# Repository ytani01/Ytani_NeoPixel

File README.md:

# Ytani NeoPixel Library

## 1. for Python3 on Raspberry Pi
  [rpi-python3/](rpi-python3/)

## 2. for C++ on Arduino, ESP32, ATTiny etc..
  [arduino-etc/](arduino-etc/)

### 2.0 !! 重要 !!

* NeoPixelライブラリの実行で、割り込みが効かなくなる
  ``show()``の直後に、``interrupts()`` または ``sei()``をすること！
* ATTiny85のメモリ(RAM)不足で、挙動がおかしくなる。

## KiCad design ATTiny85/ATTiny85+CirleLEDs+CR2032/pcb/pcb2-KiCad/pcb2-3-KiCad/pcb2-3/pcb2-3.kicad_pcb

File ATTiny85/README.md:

# ATTiny85

## Arduio IEDによる書き込み

### ブートローダー

### ボード設定

- [ツール]-[ボード]-[ATTinyCore]-[ATTiny25/45/85 (No bootloader)]
- [ツール]-[Chip]-[ATTiny85]
- [ツール]-[書き込み装置]-[Arduino Leo/Micro as ISP (ATmega32U4)]

### ブートローダーの書き込み (最初の一回だけ)

- [ツール]-[ブートローダーを書き込む]

### 書き込み

- [スケッチ]-[書き込み装置を使って書き込む] (Ctrl+Shift+U)

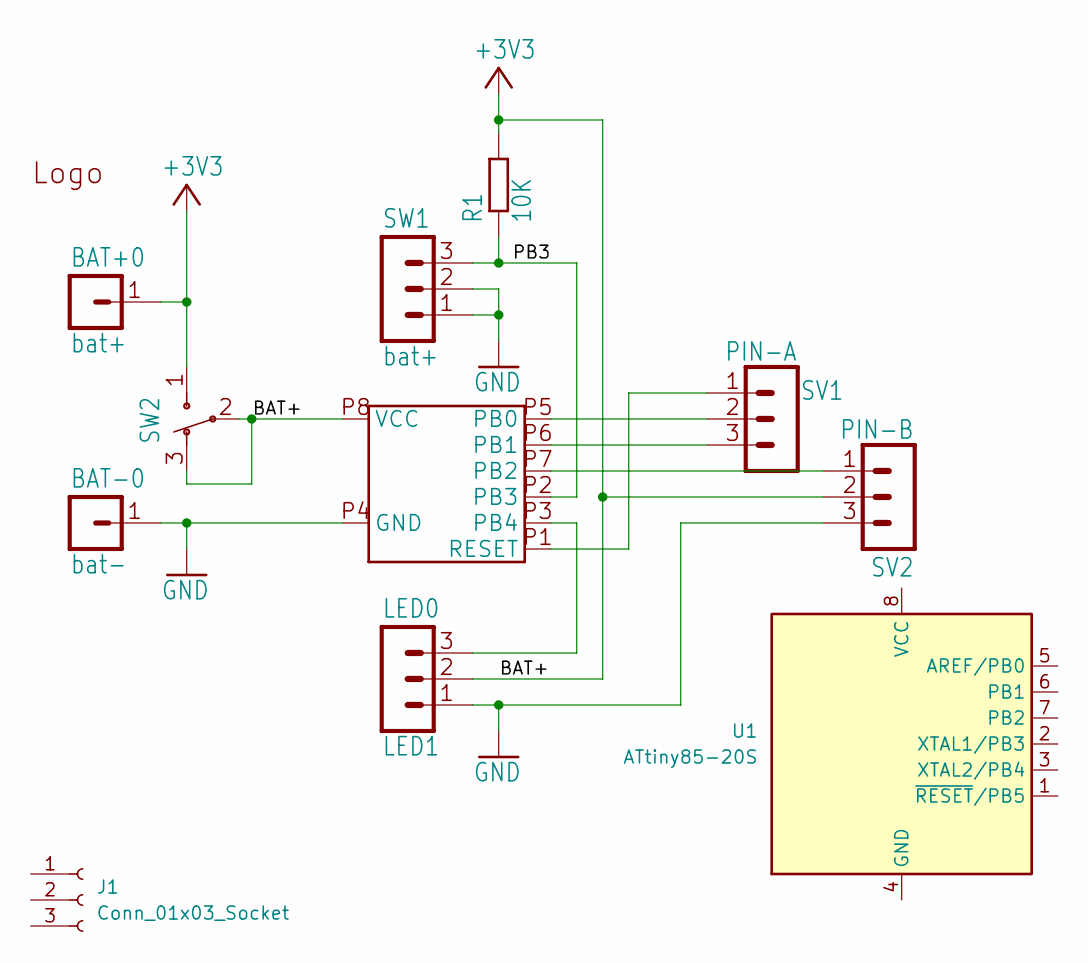
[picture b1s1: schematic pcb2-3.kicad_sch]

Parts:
ATTINY85-1: ATTINY85; ATTINY85-20SUR
BAT+0: bat+; PINHEAD-MA01-1
BAT-0: bat-; PINHEAD-MA01-1
J1: Conn_01x03_Socket
LED0: LED1; PINHEAD-MA03-1
LOGO1: LOGO-YT; LOGO-YT1
R1: 10K; M3216
SV1: PIN-A; PINHEAD-MA03-1
SV2: PIN-B; PINHEAD-MA03-1
SW1: bat+; PINHEAD-MA03-1
SW2: POWER; SW3-1
U1: ATtiny85-20S; SOIC-8_5.3x5.3mm_P1.27mm

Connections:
+3V3: ATTINY85-1.P8 (VCC), BAT+0.1, LED0.2, R1.2, SV2.2, SW2.1, SW2.2, SW2.3
/PB3: ATTINY85-1.P2 (PB3), R1.1, SW1.3
GND: ATTINY85-1.P4 (GND), BAT-0.1, LED0.1, SV2.3, SW1.1, SW1.2
unnamed: ATTINY85-1.P5 (PB0), SV1.2
unnamed: ATTINY85-1.P6 (PB1), SV1.3
unnamed: ATTINY85-1.P7 (PB2), SV2.1
unnamed: ATTINY85-1.P3 (PB4), LED0.3
unnamed: ATTINY85-1.P1 (RESET), SV1.1

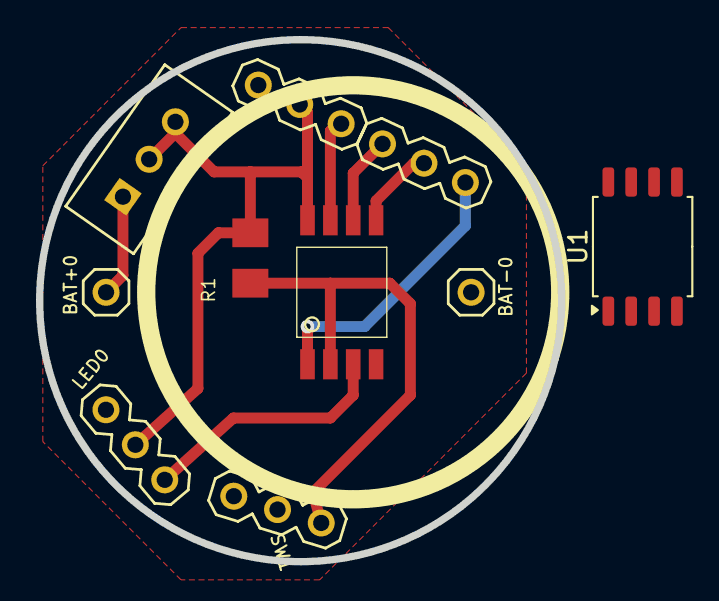
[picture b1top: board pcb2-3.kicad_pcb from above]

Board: 2 copper layers, 29.0 x 29.0 mm, 11 parts (1 on the bottom side), 8 nets.

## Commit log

2021-09-01 in preparation
2021-09-01 test1.py
2021-09-01 version 0.0.1
2021-09-01 UPD: README.md
2021-09-02 UPD: yt_neopixel.py
2021-09-02 UPD: rename
2021-09-02 UPD:
2021-09-02 ADD: test2
2021-09-02 UPD: __main__.py
2021-09-02 0.0.2
2021-09-02 START: 0.0.3
2021-09-02 ADD: Ytani_NeoPixel_Color class
2021-09-02 START: 0.0.4
2021-09-03 COMMIT: 0.0.4
2021-09-03 START: 0.0.5
2021-09-03 ADD: examples/robot_eye1.py
2021-09-05 UPD: tests
2021-09-05 START: 0.0.6
2021-09-05 ADD: class RobotEye_Cirle7LEDs
2021-09-05 START: 0.0.7
2021-09-06 UPD: class RobotEye_Cirle7LEDs
2021-09-06 UPD: robot_eyes_7leds.py
2021-09-06 FIX: install.sh
2021-09-06 START: 0.0.8
2021-09-06 ADD: RGB test
2021-09-06 START: 0.0.9
2021-09-06 UPD: for CuiLib 0.0.3
2021-09-06 START: 0.0.10
2021-09-06 START: 0.1.0
2021-09-07 UPD: README.md, setup.cfg
2021-09-10 START: 0.1.1
2021-09-12 UPD: add offset option to robot_eye1
2021-09-12 START: 0.1.2
2021-09-12 UPD: rgb-test
2021-09-12 START: 0.1.3
2021-09-13 UPD: robot_eye1
2021-09-13 START: 1.1.4
2021-09-13 START: 0.1.5
2021-09-15 UPD: update
2021-09-15 START: 1.1.6
2021-09-15 UPD: robot-eye
2021-09-16 UPD: dir tree
2021-09-16 ADD: arduino-c++
2021-09-18 ADD: color_wave2.ino
2021-09-18 UPD: color_wave2.ino
2021-09-20 UPD: demo
2021-09-20 UPD: robot_eye
2021-09-20 START: 0.1.7
2021-09-23 UPD: robot_eye_7leds.py
2021-09-25 ADD: Circle7LEDs-1.jpg
2021-09-28 START: 0.1.8
2021-09-28 ADD: interactive mode for robot-eye
2021-10-02 ADD: color_wave_4led/
2021-10-03 UPD: color_wave/
2021-10-05 ADD: tests/touch1
2021-10-06 UPD: tests/color_wave_ATTiny
2021-10-08 ADD: tests/switch1
2021-10-09 ADD: pcb
2021-10-09 ADD: pcb/bootloader
2021-10-09 UPD: .gitignore
2021-10-12 ADD: tests/color_wave3
2021-10-12 UPD: color_wave3
2021-11-18 UPD: pcb
2021-11-18 ADD: M5StampPico/
2021-11-18 ADD: M5StampPico/analogRead1/
2021-11-19 ADD: M5StampPico/sensor-NeoPixel/
2021-12-05 ADD: badge1/
2021-12-06 ADD: switch2/
2021-12-06 ADD: ATTiny-pinout.jpg
2021-12-07 ADD: switch3
2021-12-07 ADD: Mode_SingleColor
2021-12-07 UPD: switch3/
2021-12-10 ADD: pcb2/
2021-12-11 ADD: pcb3/
2021-12-12 ADD: LedLight2/
2021-12-12 UPD: LedLight2/
2021-12-13 ADD: LedLight3/Mode_White
2021-12-14 UPD: LedLight3/
2021-12-18 UPD: init.el
2021-12-20 ADD: ATTiny85/.../pcb2-2/
2021-12-22 ADD: LedLight4/
2021-12-22 UPD: LedLight4/ .. EEPROM
2021-12-22 UPD: rename LedLight4/ to LedLight/
2021-12-23 ADD: LedLight/Mode_Random1
2021-12-23 UPD: LedLight/Mode_Random1
2021-12-24 UPD: LedLight/
2022-01-13 START: LedLight3/
2022-01-13 ADD: pcb2-3/
2022-01-14 ADD: LedLight3/
2022-01-15 UPD: M5StampPico/color_wave3/
2022-01-15 ADD: M5StampPico/temp_sensor1/
2022-01-16 UPD: M5StampPico/temp_sensor1/
2022-03-19 START: LedLight4/
2022-05-24 DEL: pcb2-4/attiny85.brd
2022-05-24 ADD: LedLight5/
2022-10-16 ADD: pcb4-SK6812/
2022-10-16 FIX: pcb4-SK6812/
2022-10-16 ADD: sensor-NeoPixel2/
2022-10-28 UPD: ATTiny85/color_wave/
2022-10-29 UPD: ATTiny85/
2022-10-29 UPD: ATTiny85/LedBadge/
2022-10-30 UPD: pcb2-SK6812/
2022-10-30 UPD: LedBadge2/
2022-11-06 ADD: LedBudge3/
2022-11-06 UPD: LedBudge3-*/
2022-11-09 UPD: LedBadge3-../
2022-11-09 UPD: pcb3-../
2022-11-17 ADD:ATTiny85/README.md
2022-12-03 ADD: LedBadge/image
2022-12-04 ADD: sensor-NeoPixel-simpole1
2023-01-07 plate1.svg
2023-01-07 image/pcb4.*
2023-01-07 pcb4-SK6812/pcb4.*
2023-01-09 UPD: pcb4-SK6812/
2023-01-13 UPD: directory tree
2023-01-13 UPD: pcb4-SK6812/pcb4.svg
2023-01-14 UPD: pcb4-SK6812/pcb4.pdf
2023-01-14 UPD: pcb4-SK6812/pcb4.svg:
2023-01-15 ADD: LedTimer/
2023-06-10 modeSetTimer
2023-06-10 ADD: pcb5-SK6812
2023-06-22 pcb5
2025-06-11 ADD: ATTiny85 .. pcb2-3-KiCad
2025-06-12 UPD: directory tree: pcb/
